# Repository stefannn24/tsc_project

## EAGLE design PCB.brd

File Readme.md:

InkTime Smartwatch

Hardware Functionality
Power Management

The power path begins at the USB-C connector (5V VBUS), which feeds the Li-Po charge management IC. This IC handles the safe charging cycle for the 250mAh battery. To ensure the MCU and E-paper display receive a clean and stable voltage even as the battery discharges, a DC/DC Buck/Boost regulator is utilized to provide a constant 3.3V system rail.
Compute & Connectivity

The system is driven by the nRF52840 SoC. It manages:

- I2C Bus: Used for communicating with the ultra-low-power IMU (Accelerometer).
- SPI Bus: Dedicated specifically to the E-paper display to ensure enough bandwidth for screen refreshes without interrupting other peripherals.
- USB: Routed directly to the nRF52840 for potential firmware flashing and USB-CDC communications.
- RF: A 50-ohm matched RF trace connects the MCU to a 2.4GHz Johanson SMD chip antenna for Bluetooth Low Energy (BLE) connectivity.

Peripherals

- Display: A low-power E-paper display module.
- IMU: An accelerometer is used for hardware-level step counting.
- Haptics

During the layout and routing phases of the PCB, several specific design rules and constraints were strictly applied to ensure manufacturability and signal integrity:

- Strict top-layer placement: To comply with manufacturing assembly constraints, 100% of the components were placed exclusively on the Top layer.
- Trace width constraints for power: All power delivery networks (VCC, VBUS, 3V3, VBAT) were manually routed using a minimum trace width of 0.3mm. This ensures adequate current handling, especially during peak loads from the shaker motor. Data signals were routed at 0.15mm.
- Antenna keepout zone: The 2.4GHz SMD antenna was placed strictly on the outer edge of the PCB. A complete keepout area was enforced underneath the antenna on all layers.
- Decoupling proximity: All 100nF (0201 package) decoupling capacitors were placed as physically close to the nRF52840 and IMU power pins as mechanically possible to filter out high-frequency switching noise.

(The complete machine-readable .bom and .cpl files are located in the /Manufacturing directory).

License
This project is licensed under the MIT License. See the LICENSE file for details.

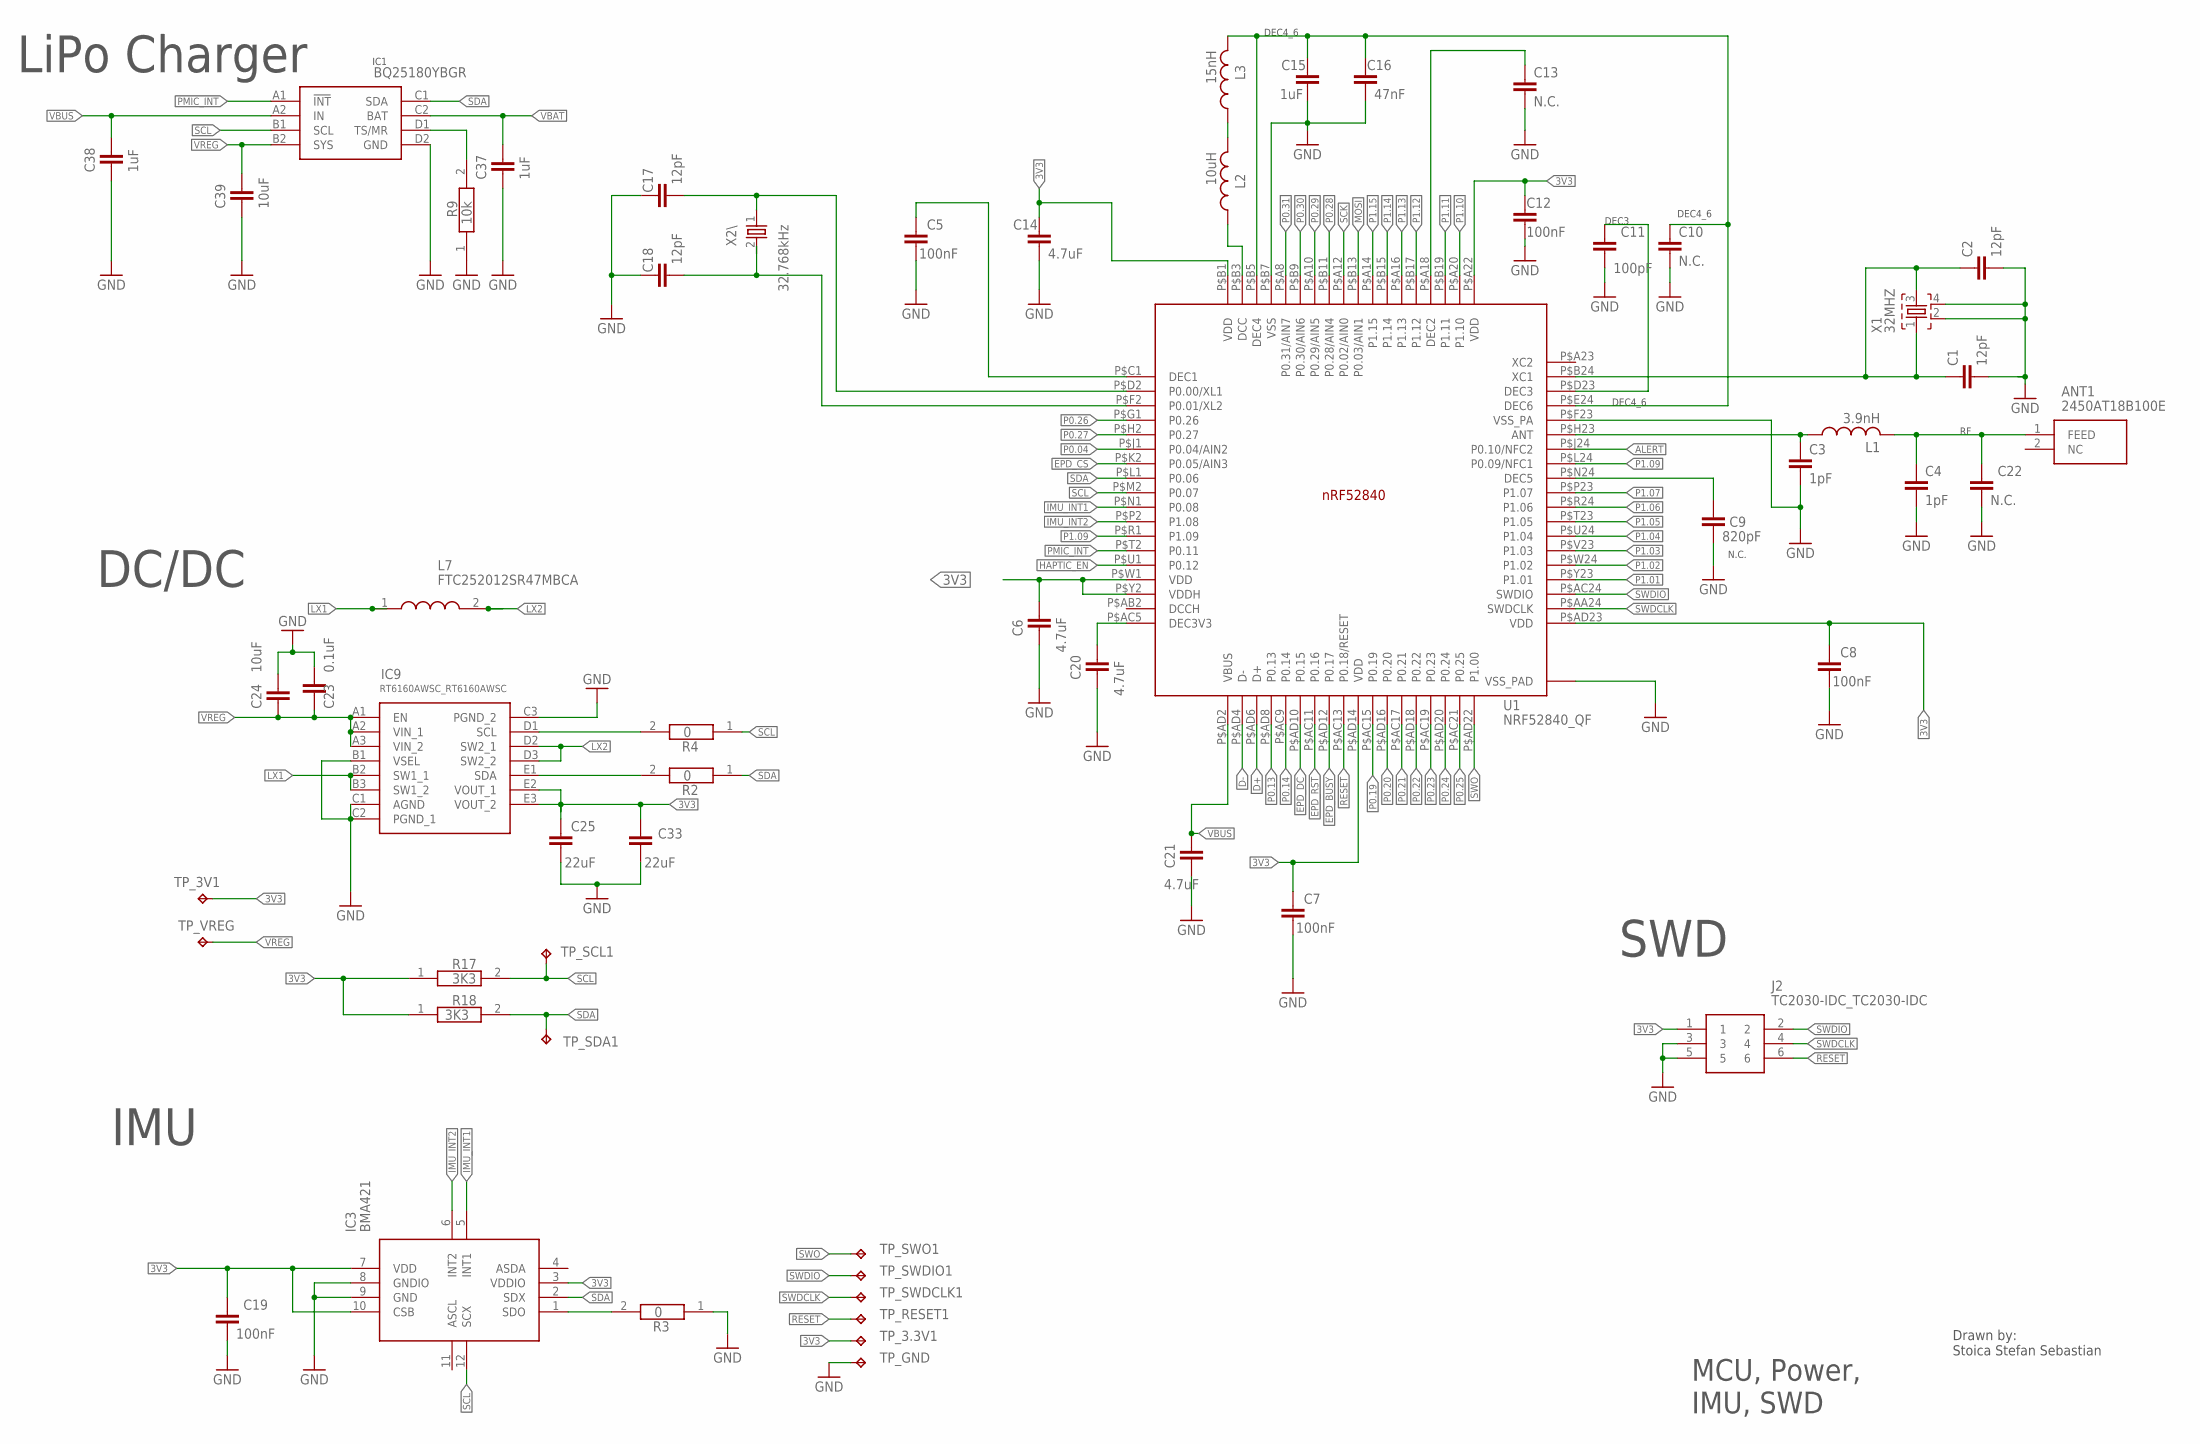
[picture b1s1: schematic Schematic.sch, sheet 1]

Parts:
ANT1: 2450AT18B100E; 2450AT18B100E_ANTC3216X140N
C1, C2, C17, C18: 12pF; NORDIC_NRF_3_RESC0201_N
C3, C4: 1pF; NORDIC_NRF_3_RESC0201_N
C5, C7, C8, C12, C19: 100nF; NORDIC_NRF_3_RESC0201_N
C6, C14, C20, C21: 4.7uF; NORDIC_NRF_3_RESC0402_N
C9: 820pF; NORDIC_NRF_3_RESC0201_N
C10, C13, C22: N.C.; NORDIC_NRF_3_RESC0201_N
C11: 100pF; NORDIC_NRF_3_RESC0201_N
C15, C37, C38: 1uF; NORDIC_NRF_3_RESC0402_N
C16: 47nF; NORDIC_NRF_3_RESC0201_N
C23: 0.1uF; NORDIC_NRF_3_RESC0201_N
C24: 10uF; NORDIC_NRF_3_RESC0402_N
C25, C33: 22uF; NORDIC_NRF_3_RESC0603_N
C39: 10uF; NORDIC_NRF_3_RESC0603_N
IC1: BQ25180YBGR; BQ25180YBGR_BGA8C40P2X4_100X155X50
IC3: BMA421; BMA423_BMA423; MANUFACTURER_PART_NUMBER BMA421; MOUSER_PART_NUMBER 262-BMA421
IC9: RT6160AWSC_RT6160AWSC; RT6160AWSC_BGA15C40P3X5_140X230X60
J2: TC2030-IDC_TC2030-IDC; TC2030-IDC_TC2030IDC
L1: 3.9nH; NORDIC_NRF_2_RESC0402_L
L2: 10uH; NORDIC_NRF_2_RESC0603_N
L3: 15nH; NORDIC_NRF_2_RESC0402_L
L7: FTC252012SR47MBCA; MLP2016SR47MT0S1_INDC2016X100N
R2, R3, R4: 0; CPF0201D7K68C1_0201
R9: 10k; CPF0201D7K68C1_0201
R17, R18: 3K3; CPF0201D7K68C1_0201
TP_3.3V1, TP_3V1: HECTOR_WATCH_1_TPTP20R; HECTOR_WATCH_1_TP20R
TP_GND: HECTOR_WATCH_1_TPTP20R; HECTOR_WATCH_1_TP20R
TP_RESET1: HECTOR_WATCH_1_TPTP20R; HECTOR_WATCH_1_TP20R
TP_SCL1: HECTOR_WATCH_1_TPTP20R; HECTOR_WATCH_1_TP20R
TP_SDA1: HECTOR_WATCH_1_TPTP20R; HECTOR_WATCH_1_TP20R
TP_SWDCLK1: HECTOR_WATCH_1_TPTP20R; HECTOR_WATCH_1_TP20R
TP_SWDIO1: HECTOR_WATCH_1_TPTP20R; HECTOR_WATCH_1_TP20R
TP_SWO1: HECTOR_WATCH_1_TPTP20R; HECTOR_WATCH_1_TP20R
TP_VREG: HECTOR_WATCH_1_TPTP20R; HECTOR_WATCH_1_TP20R
U1: NRF52840_QF; NORDIC_NRF_4_AQFN50P700X700X85_HS-74N
X1: 32MHZ; NORDIC_NRF_BT-XTAL_2016_N
X2\: 32.768kHz; NORDIC_NRF_1_XTAL_3215_N

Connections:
3V3: C6.1, C7.1, C8.1, C12.2, C14.1, C19.2, C25.1, C33.1, IC3.3 (VDDIO), IC3.7 (VDD), IC3.10 (CSB), IC9.E2 (VOUT_1), IC9.E3 (VOUT_2), J2.1, R17.1, R18.1, TP_3.3V1.TP, TP_3V1.TP, U1.P$A22 (VDD), U1.P$AD14 (VDD), U1.P$AD23 (VDD), U1.P$B1 (VDD), U1.P$W1 (VDD), U1.P$Y2 (VDDH); also elsewhere on the board
ALERT: U1.P$J24 (P0.10/NFC2); also elsewhere on the board
D+: U1.P$AD6 (D+); also elsewhere on the board
D-: U1.P$AD4 (D-); also elsewhere on the board
EPD_BUSY: U1.P$AD12 (P0.17); also elsewhere on the board
EPD_CS: U1.P$K2 (P0.05/AIN3); also elsewhere on the board
EPD_DC: U1.P$AD10 (P0.15); also elsewhere on the board
EPD_RST: U1.P$AC11 (P0.16); also elsewhere on the board
GND: C1.2, C2.2, C3.1, C4.1, C5.2, C6.2, C7.2, C8.2, C9.1, C10.1, C11.1, C12.1, C13.1, C14.2, C15.2, C16.1, C17.1, C18.1, C19.1, C20.2, C21.2, C22.1, C23.1, C24.1, C25.2, C33.2, C37.2, C38.2, C39.2, IC1.D2 (GND), IC3.8 (GNDIO), IC3.9 (GND), IC9.B1 (VSEL), IC9.C1 (AGND), IC9.C2 (PGND_1), IC9.C3 (PGND_2), J2.3, J2.5, R3.1, R9.1, TP_GND.TP, U1.P$74 (VSS_PAD), U1.P$75 (VSS_PAD), U1.P$76 (VSS_PAD), U1.P$77 (VSS_PAD), U1.P$78 (VSS_PAD), U1.P$79 (VSS_PAD), U1.P$80 (VSS_PAD), U1.P$81 (VSS_PAD), U1.P$82 (VSS_PAD), U1.P$83 (VSS_PAD), U1.P$84 (VSS_PAD), U1.P$85 (VSS_PAD), U1.P$86 (VSS_PAD), U1.P$87 (VSS_PAD), U1.P$88 (VSS_PAD), U1.P$89 (VSS_PAD), U1.P$90 (VSS_PAD), U1.P$B7 (VSS), U1.P$F23 (VSS_PA), X1.2, X1.4; also elsewhere on the board
HAPTIC_EN: U1.P$U1 (P0.12); also elsewhere on the board
LX1: IC9.B2 (SW1_1), IC9.B3 (SW1_2), L7.1
LX2: IC9.D2 (SW2_1), IC9.D3 (SW2_2), L7.2
MOSI: U1.P$B13 (P0.03/AIN1); also elsewhere on the board
unnamed: C3.2, L1.1, U1.P$H23 (ANT)
unnamed: ANT1.1 (FEED), C4.2, C22.2, L1.2
unnamed: C11.2, U1.P$D23 (DEC3)
unnamed: C1.1, C2.1, U1.P$B24 (XC1), X1.1, X1.3
unnamed: C9.2, U1.P$N24 (DEC5)
unnamed: L2.1, U1.P$B3 (DCC)
unnamed: IC1.D1 (TS/MR), R9.2
unnamed: IC9.D1 (SCL), R4.2
unnamed: IC9.E1 (SDA), R2.2
unnamed: IC3.1 (SDO), R3.2
unnamed: C5.1, U1.P$C1 (DEC1)
unnamed: C17.2, U1.P$D2 (P0.00/XL1), X2\.1
unnamed: C20.1, U1.P$AC5 (DEC3V3)
unnamed: C18.2, U1.P$F2 (P0.01/XL2), X2\.2
unnamed: L2.2, L3.1
unnamed: C10.2, C15.1, C16.2, L3.2, U1.P$B5 (DEC4), U1.P$E24 (DEC6)
unnamed: C13.2, U1.P$A18 (DEC2)
P0.04: U1.P$J1 (P0.04/AIN2)
P0.13: U1.P$AD8 (P0.13); also elsewhere on the board
P0.14: U1.P$AC9 (P0.14); also elsewhere on the board
P0.19: U1.P$AC15 (P0.19)
P0.20: U1.P$AD16 (P0.20)
P0.21: U1.P$AC17 (P0.21)
P0.22: U1.P$AD18 (P0.22)
P0.23: U1.P$AC19 (P0.23)
P0.24: U1.P$AD20 (P0.24)
P0.25: U1.P$AC21 (P0.25)
P0.26: U1.P$G1 (P0.26)
P0.27: U1.P$H2 (P0.27)
P0.28: U1.P$B11 (P0.28/AIN4)
P0.29: U1.P$A10 (P0.29/AIN5)
P0.30: U1.P$B9 (P0.30/AIN6)
P0.31: U1.P$A8 (P0.31/AIN7)
P1.01: U1.P$Y23 (P1.01); also elsewhere on the board
P1.02: U1.P$W24 (P1.02); also elsewhere on the board
P1.03: U1.P$V23 (P1.03)
P1.04: U1.P$U24 (P1.04)
P1.05: U1.P$T23 (P1.05)
P1.06: U1.P$R24 (P1.06)
P1.07: U1.P$P23 (P1.07)
P1.09: U1.P$L24 (P0.09/NFC1), U1.P$R1 (P1.09)
P1.10: U1.P$A20 (P1.10)
P1.11: U1.P$B19 (P1.11)
P1.12: U1.P$B17 (P1.12)
P1.13: U1.P$A16 (P1.13)
P1.14: U1.P$B15 (P1.14)
P1.15: U1.P$A14 (P1.15)
RESET: J2.6, TP_RESET1.TP, U1.P$AC13 (P0.18/RESET)
SCK: U1.P$A12 (P0.02/AIN0); also elsewhere on the board
SCL: IC1.B1 (SCL), IC3.12 (SCX), R4.1, R17.2, TP_SCL1.TP, U1.P$M2 (P0.07); also elsewhere on the board
SDA: IC1.C1 (SDA), IC3.2 (SDX), R2.1, R18.2, TP_SDA1.TP, U1.P$L1 (P0.06); also elsewhere on the board
SWDCLK: J2.4, TP_SWDCLK1.TP, U1.P$AA24 (SWDCLK)
SWDIO: J2.2, TP_SWDIO1.TP, U1.P$AC24 (SWDIO)
SWO: TP_SWO1.TP, U1.P$AD22 (P1.00)
VBAT: C37.1, IC1.C2 (BAT); also elsewhere on the board
VBUS: C21.1, C38.1, IC1.A2 (IN), U1.P$AD2 (VBUS); also elsewhere on the board
VREG: C23.2, C24.2, C39.1, IC1.B2 (SYS), IC9.A1 (EN), IC9.A2 (VIN_1), IC9.A3 (VIN_2), TP_VREG.TP

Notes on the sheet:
DC/DC
SWD
N.C.
DEC3
DEC4_6
LiPo Charger
IMU
Drawn by: Stoica Stefan Sebastian
IC1
MCU, Power, IMU, SWD

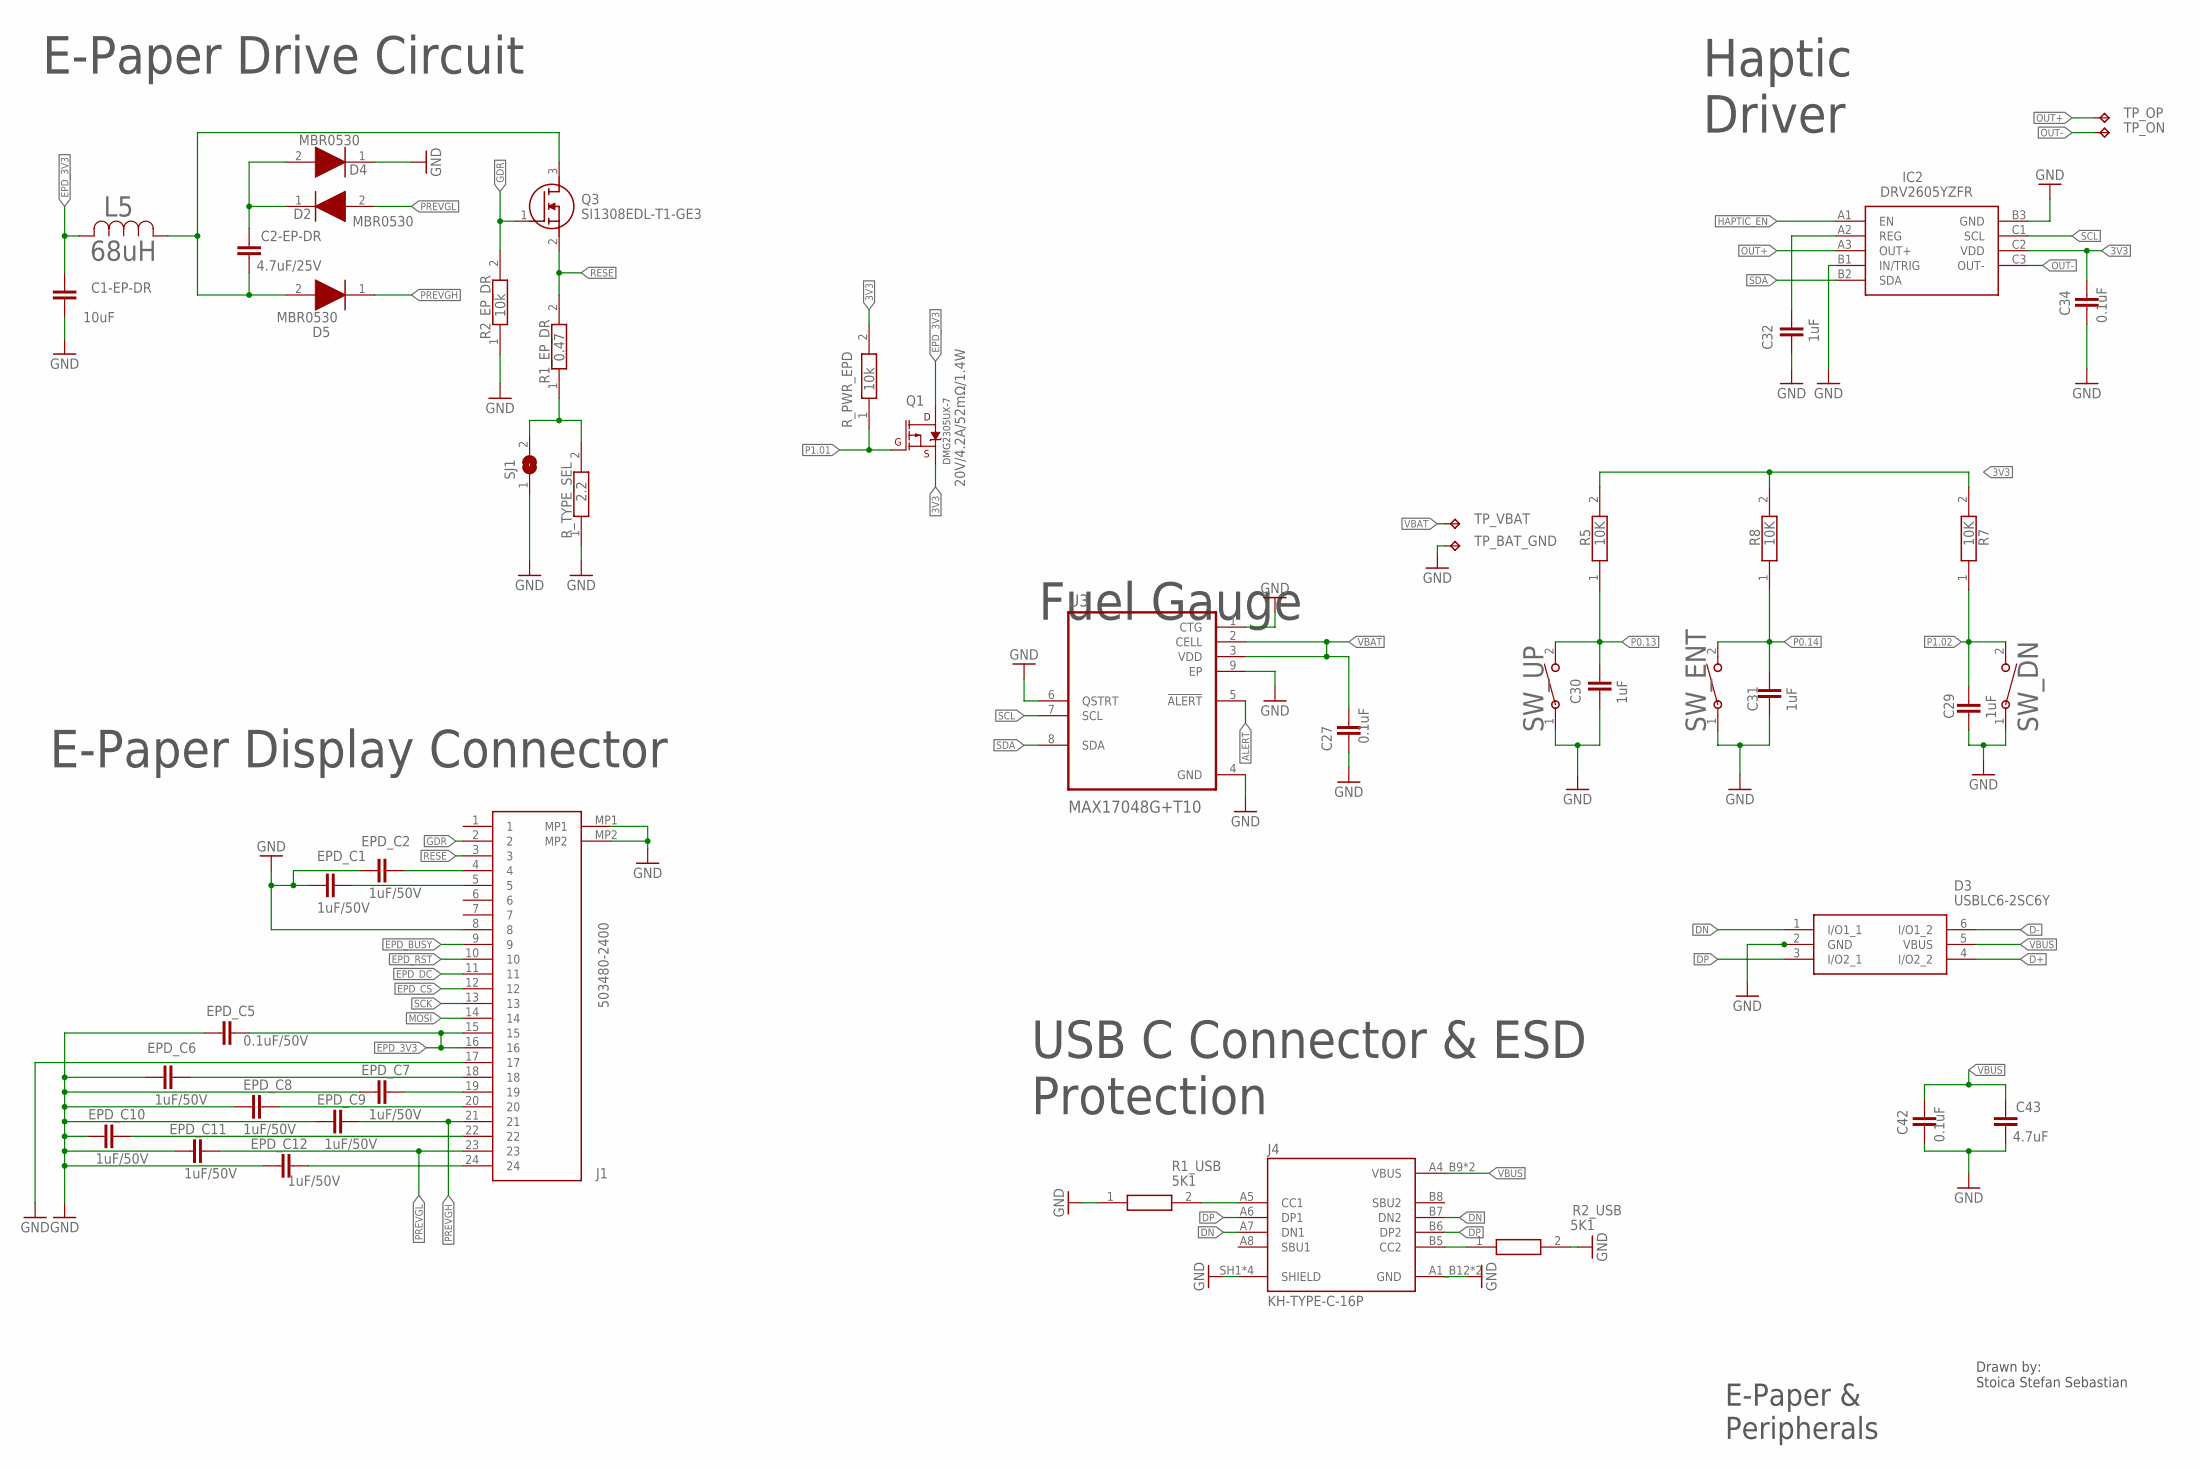
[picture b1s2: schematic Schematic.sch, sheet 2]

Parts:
C1-EP-DR: 10uF; NORDIC_NRF_3_RESC0402_N
C2-EP-DR: 4.7uF/25V; NORDIC_NRF_3_RESC0603_N
C27, C34, C42: 0.1uF; NORDIC_NRF_3_RESC0201_N
C29, C30, C31, C32: 1uF; NORDIC_NRF_3_RESC0402_N
C43: 4.7uF; NORDIC_NRF_3_RESC0402_N
D2, D4, D5: MBR0530; ESP32_C6_LIBRARY_5_SOD3716X135N
D3: USBLC6-2SC6Y; ESP32_C6_LIBRARY_3_SOT95P280X145-6N
EPD_C1, EPD_C2, EPD_C6, EPD_C7, EPD_C8, EPD_C9, EPD_C10, EPD_C11, EPD_C12: 1uF/50V; NORDIC_NRF_3_RESC0402_N
EPD_C5: 0.1uF/50V; NORDIC_NRF_3_RESC0402_N
IC2: DRV2605YZFR; DRV2605YZFR_BGA9C50P3X3_144X144X62
J1: 503480-2400; 503480-2400_5034802400
J4: KH-TYPE-C-16P; KH-TYPE-C-16P_KINGHELM_KH-TYPE-C-16P
L5: 68uH; ESP32_C6_LIBRARY_2_IND_4828-WE-TPC_WRE
Q1: 20V/4.2A/52mΩ/1.4W; ESP32_C6_LIBRARY_4_ESP32_C6_LIBRARY_4_ESP32_C6_LIBRARY_4_ES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
Q3: SI1308EDL-T1-GE3; ESP32_C6_LIBRARY_6_SOT65P210X110-3N
R1_EP_DR: 0.47; CPF0201D7K68C1_0201
R1_USB, R2_USB: 5K1; CPF0201D7K68C1_0201
R2_EP_DR: 10k; CPF0201D7K68C1_0201
R5, R7, R8: 10K; CPF0201D7K68C1_0201
R_PWR_EPD: 10k; CPF0201D7K68C1_0201
R_TYPE_SEL: 2.2; CPF0201D7K68C1_0201
SJ1: ESP32_C6_LIBRARY_7_JUMPER_SJ
SW_DN: 2025-10-22_07-23-44_LIBRARY_EVP-AKE31ASW_EVP-AKE3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; 2025-10-22_07-23-44_LIBRARY_SW_EVP-AKE31A_PAN
SW_ENT: 2025-10-22_07-23-44_LIBRARY_EVP-AKE31ASW_EVP-AKE3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; 2025-10-22_07-23-44_LIBRARY_SW_EVP-AKE31A_PAN
SW_UP: 2025-10-22_07-23-44_LIBRARY_EVP-AKE31ASW_EVP-AKE3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; 2025-10-22_07-23-44_LIBRARY_SW_EVP-AKE31A_PAN
TP_BAT_GND: HECTOR_WATCH_1_TPTP20R; HECTOR_WATCH_1_TP20R
TP_ON: HECTOR_WATCH_1_TPTP20R; HECTOR_WATCH_1_TP20R
TP_OP: HECTOR_WATCH_1_TPTP20R; HECTOR_WATCH_1_TP20R
TP_VBAT: HECTOR_WATCH_1_TPTP20R; HECTOR_WATCH_1_TP20R
U3: MAX17048G+T10; ESP32_C6_LIBRARY_SON50P200X200X80-9N

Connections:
3V3: C34.1, IC2.C2 (VDD), Q1.2 (S), R5.2, R7.2, R8.2, R_PWR_EPD.2; also elsewhere on the board
ALERT: U3.5 (!ALERT); also elsewhere on the board
D+: D3.4 (I/O2_2); also elsewhere on the board
D-: D3.6 (I/O1_2); also elsewhere on the board
DN: D3.1 (I/O1_1), J4.A7 (DN1), J4.B7 (DN2)
DP: D3.3 (I/O2_1), J4.A6 (DP1), J4.B6 (DP2)
EPD_3V3: C1-EP-DR.1, EPD_C5.2, J1.15, J1.16, L5.2, Q1.3 (D); also elsewhere on the board
EPD_BUSY: J1.9; also elsewhere on the board
EPD_CS: J1.12; also elsewhere on the board
EPD_DC: J1.11; also elsewhere on the board
EPD_RST: J1.10; also elsewhere on the board
GDR: J1.2, Q3.1 (G), R2_EP_DR.2
GND: C1-EP-DR.2, C27.1, C29.2, C30.1, C31.1, C32.1, C34.2, C42.2, C43.2, D3.2 (GND), D4.1 (K), EPD_C1.1, EPD_C2.1, EPD_C5.1, EPD_C6.1, EPD_C7.1, EPD_C8.1, EPD_C9.1, EPD_C10.1, EPD_C11.1, EPD_C12.1, IC2.B1 (IN/TRIG), IC2.B3 (GND), J1.8, J1.17, J1.MP1, J1.MP2, J4.A1_B12 (GND), J4.A12_B1 (GND), J4.SH1 (SHIELD), J4.SH2 (SHIELD), J4.SH3 (SHIELD), J4.SH4 (SHIELD), R1_USB.1, R2_EP_DR.1, R2_USB.2, R_TYPE_SEL.1, SJ1.1, SW_DN.1, SW_ENT.1, SW_UP.1, TP_BAT_GND.TP, U3.1 (CTG), U3.4 (GND), U3.6 (QSTRT), U3.9 (EP); also elsewhere on the board
HAPTIC_EN: IC2.A1 (EN); also elsewhere on the board
MOSI: J1.14; also elsewhere on the board
unnamed: J4.A5 (CC1), R1_USB.2
unnamed: J4.B5 (CC2), R2_USB.1
unnamed: C2-EP-DR.2, D5.2 (A), L5.1, Q3.3 (D)
unnamed: EPD_C6.2, J1.18
unnamed: EPD_C7.2, J1.19
unnamed: EPD_C8.2, J1.20
unnamed: C2-EP-DR.1, D2.1 (K), D4.2 (A)
unnamed: EPD_C2.2, J1.4
unnamed: EPD_C1.2, J1.5
unnamed: R1_EP_DR.1, R_TYPE_SEL.2, SJ1.2
unnamed: EPD_C10.2, J1.22
unnamed: EPD_C12.2, J1.24
unnamed: C32.2, IC2.A2 (REG)
OUT+: IC2.A3 (OUT+), TP_OP.TP
OUT-: IC2.C3 (OUT-), TP_ON.TP
P0.13: C30.2, R5.1, SW_UP.2; also elsewhere on the board
P0.14: C31.2, R8.1, SW_ENT.2; also elsewhere on the board
P1.01: Q1.1 (G), R_PWR_EPD.1; also elsewhere on the board
P1.02: C29.1, R7.1, SW_DN.2; also elsewhere on the board
PREVGH: D5.1 (K), EPD_C9.2, J1.21
PREVGL: D2.2 (A), EPD_C11.2, J1.23
RESE: J1.3, Q3.2 (S), R1_EP_DR.2
SCK: J1.13; also elsewhere on the board
SCL: IC2.C1 (SCL), U3.7 (SCL); also elsewhere on the board
SDA: IC2.B2 (SDA), U3.8 (SDA); also elsewhere on the board
VBAT: C27.2, TP_VBAT.TP, U3.2 (CELL), U3.3 (VDD); also elsewhere on the board
VBUS: C42.1, C43.1, D3.5 (VBUS), J4.A4_B9 (VBUS), J4.A9_B4 (VBUS); also elsewhere on the board

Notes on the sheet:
DMG2305UX-7
E-Paper Drive Circuit
E-Paper Display Connector
Fuel Gauge
Haptic Driver
E-Paper & Peripherals
Drawn by: Stoica Stefan Sebastian
USB C Connector & ESD Protection

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
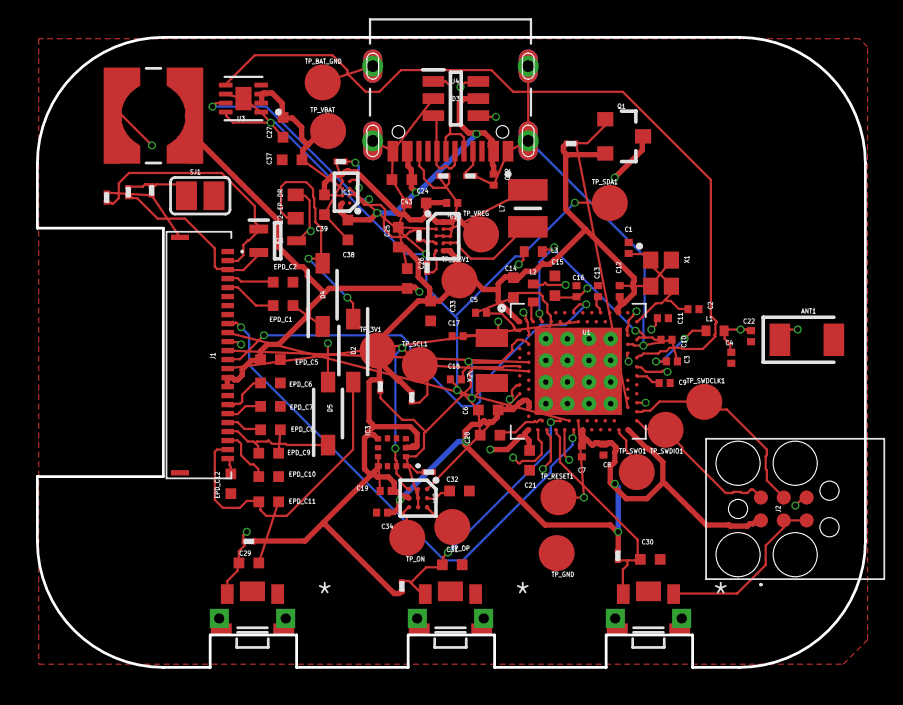
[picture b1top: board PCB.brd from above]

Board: 2 copper layers, 46.0 x 35.0 mm, 105 parts (0 on the bottom side), 67 nets.

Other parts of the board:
C26: 10uF; NORDIC_NRF_3_RESC0402_N

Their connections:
EPD_3V3: C26.1; also elsewhere on the board
GND: C26.2; also elsewhere on the board

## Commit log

2026-04-19 Updated file. Fixed issues regarding the schematic.
2026-04-19 Fix unrouted airwires in PCB.brd
    Agent-Logs-Url: https://github.com/stefannn24/tsc_project/sessions/bb13f5a2-246b-4041-b116-319afb0a67a2
2026-04-21 Create folders to respect structure of assignment
2026-04-21 Create s
2026-04-21 Add MIT License to the project

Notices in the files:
parts and their libraries:
COPYRIGHT: Copyright (C) 2024 Ultra Librarian. All rights reserved.
COPYRIGHT: Copyright (C) 2025 Ultra Librarian. All rights reserved.
